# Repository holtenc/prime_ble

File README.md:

# Prime_EXL

An ergonomic bluetooth 45% keyboard with a macro/numpad added to the left side. 

Keyboard Maintainer: [Holtenc](https://github.com/holtenc/)  
Hardware Supported: Prime_ble PCB, ATMega32u4, NRF51822 
Hardware Availability: Prototype

Make example for this keyboard (after setting up your build environment):

    make handwired/prime_ble:default

See the [build environment setup](https://docs.qmk.fm/#/getting_started_build_tools) and the [make instructions](https://docs.qmk.fm/#/getting_started_make_guide) for more information. Brand new to QMK? Start with our [Complete Newbs Guide](https://docs.qmk.fm/#/newbs).

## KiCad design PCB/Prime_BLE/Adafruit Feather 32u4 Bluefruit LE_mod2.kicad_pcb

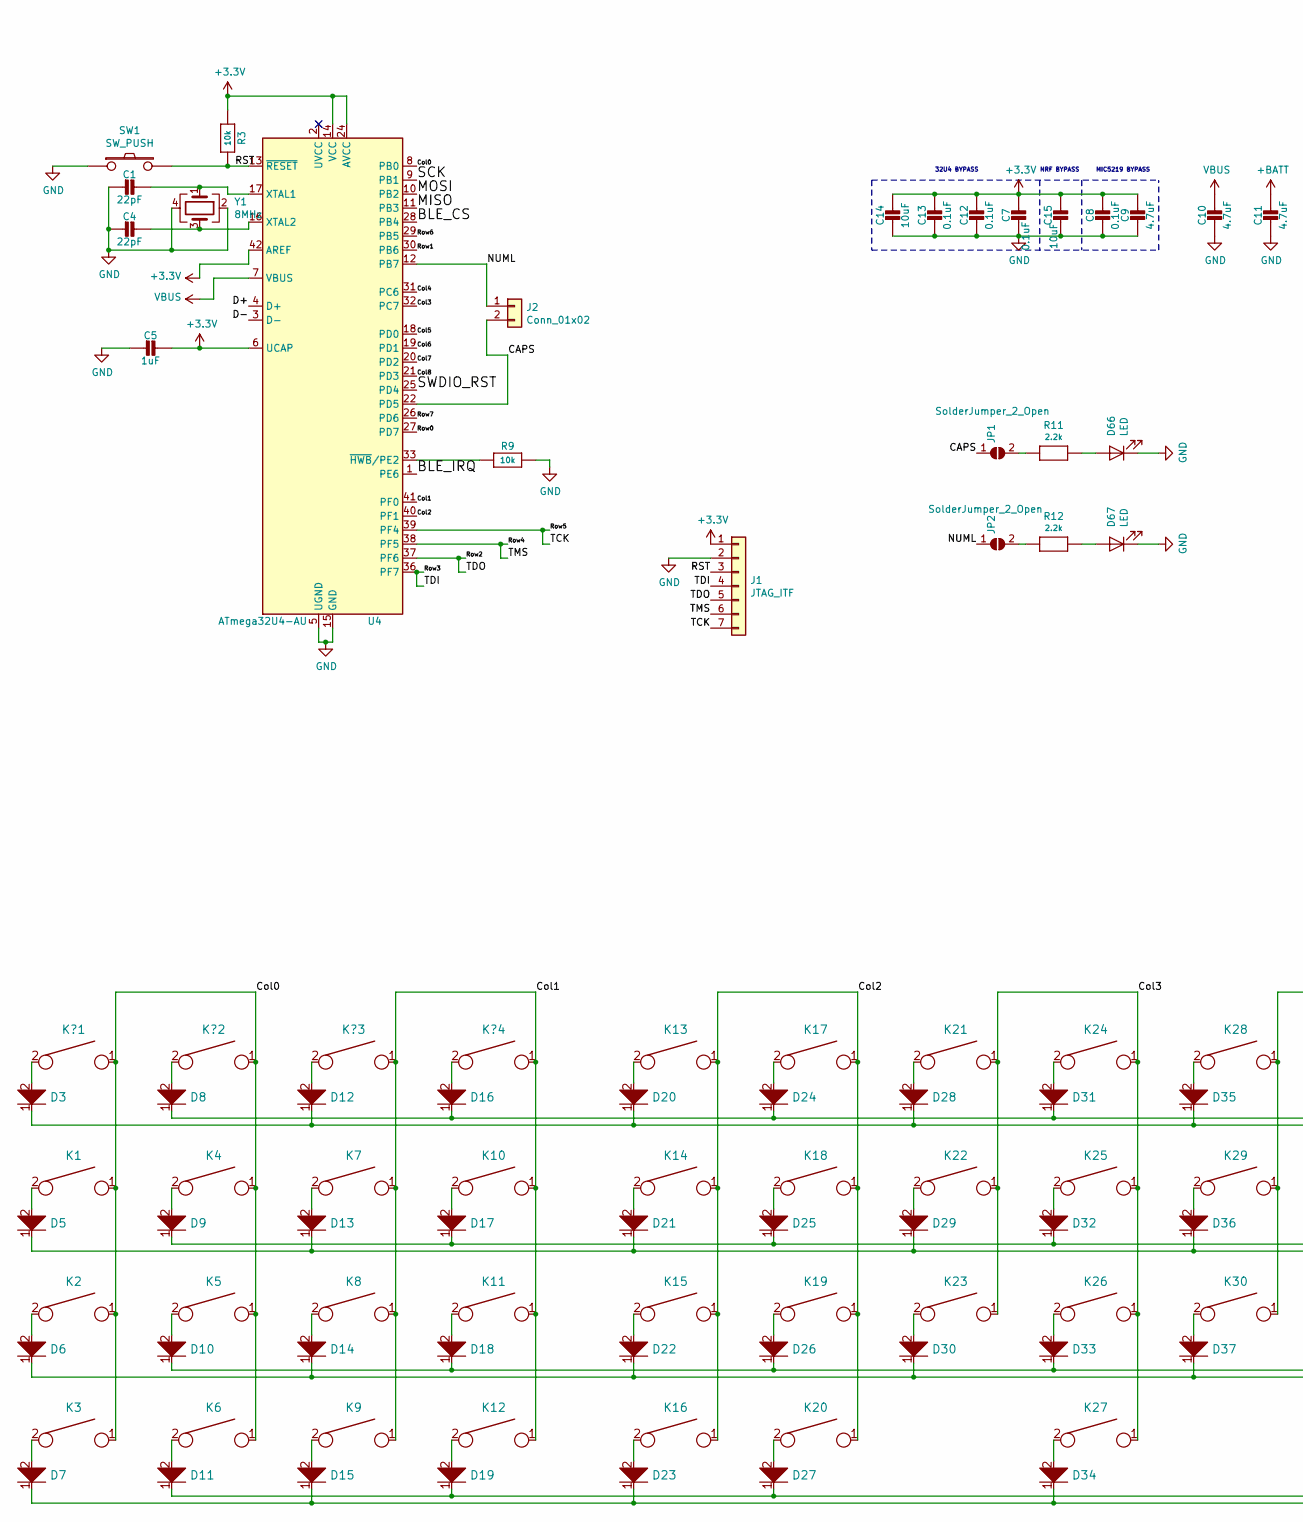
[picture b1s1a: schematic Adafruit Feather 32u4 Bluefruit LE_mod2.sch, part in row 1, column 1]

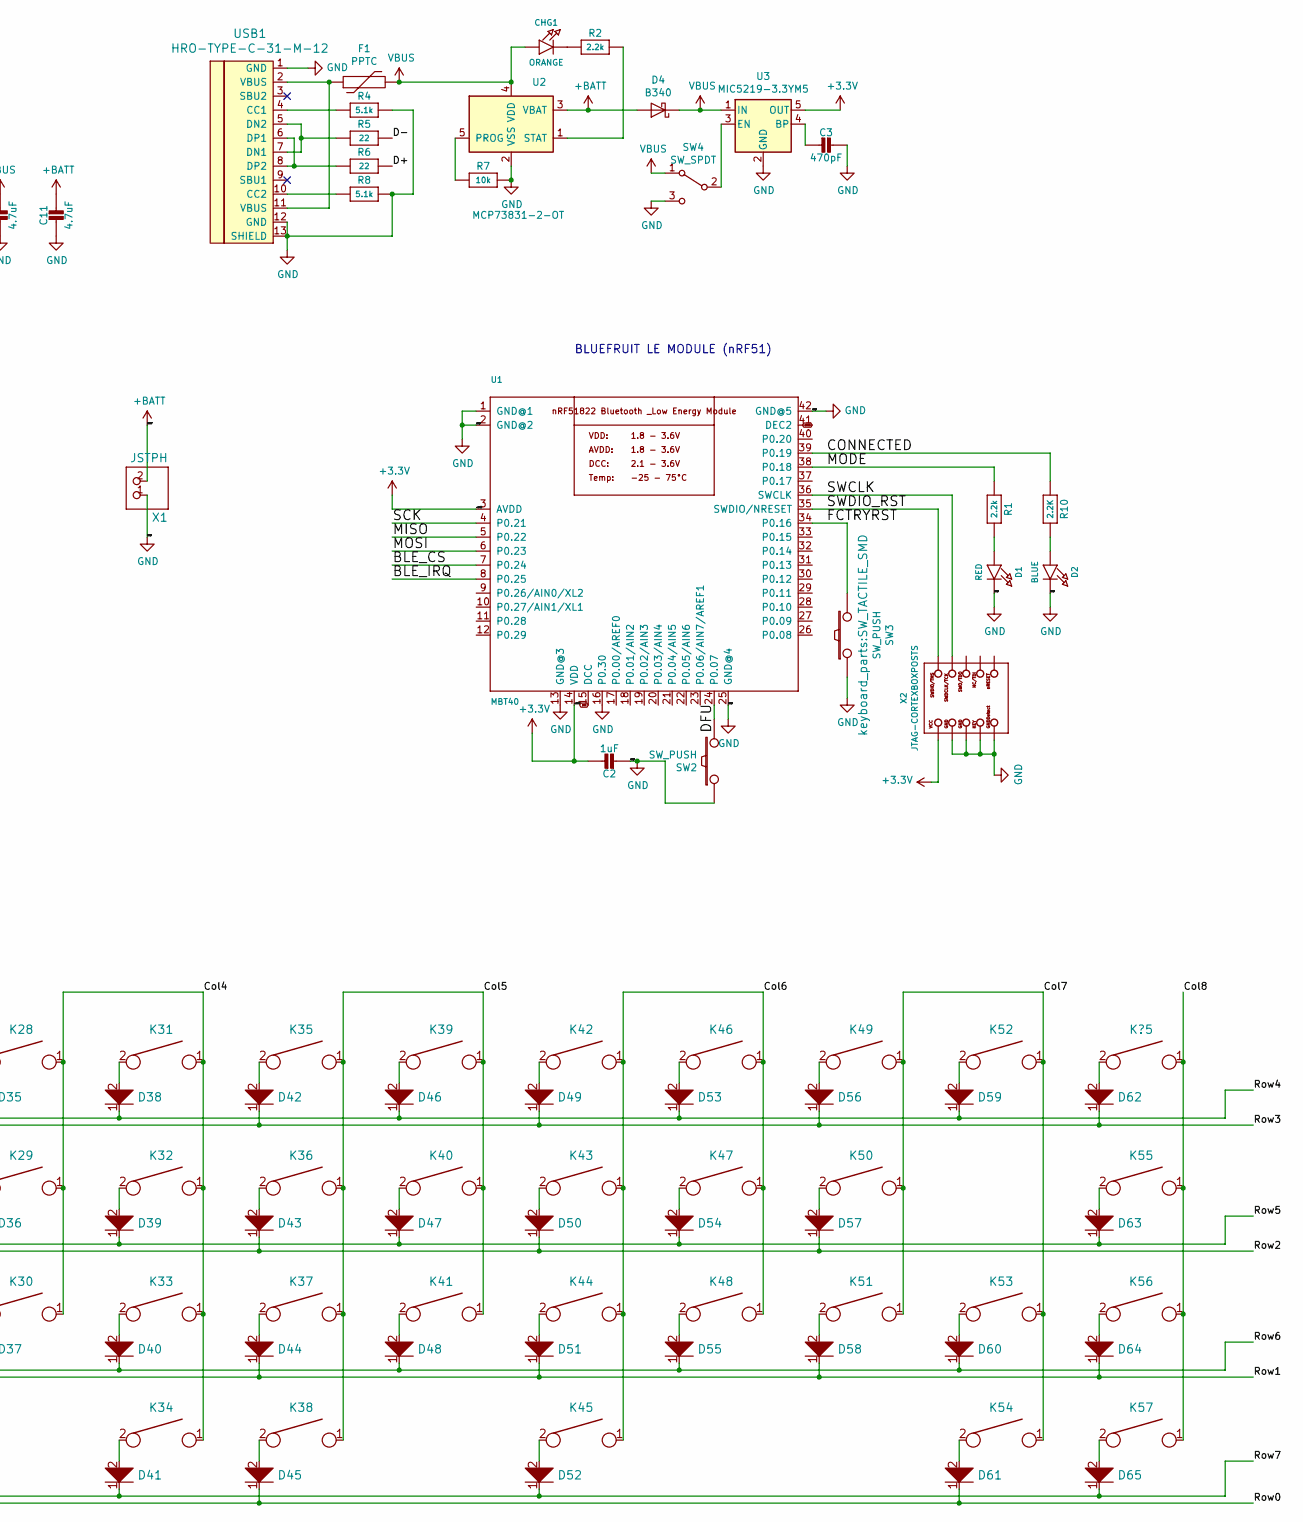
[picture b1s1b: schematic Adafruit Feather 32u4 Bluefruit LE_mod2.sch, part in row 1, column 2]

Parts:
C1, C4: 22pF; C_0603_1608Metric_Pad1.05x0.95mm_HandSolder
C2, C5: 1uF; C_0603_1608Metric_Pad1.05x0.95mm_HandSolder
C3: 470pF; C_0603_1608Metric_Pad1.05x0.95mm_HandSolder
C7, C8, C12, C13: 0.1uF; C_0603_1608Metric_Pad1.05x0.95mm_HandSolder
C9: 4.7uF; C_0603_1608Metric_Pad1.05x0.95mm_HandSolder
C10, C11: 4.7uF; C_1206_3216Metric_Pad1.42x1.75mm_HandSolder
C14, C15: 10uF; C_0603_1608Metric_Pad1.05x0.95mm_HandSolder
CHG1: ORANGE; IN-S124BR_LED
D1: RED; IN-S124BR_LED
D2: BLUE; IN-S124BR_LED
D3: D; D_SOD123
D4: B340; D_SMA_Handsoldering
D5, D6, D7, D8, D9, D10, D11, D12, D13, D14, D15, D16, D17, D18, D19, D20, D21, D22, D23, D24, D25, D26, D27, D28, D29, D30, D31, D32, D33, D34, D35, D36, D37, D38, D39, D40, D41, D42, D43, D44, D45, D46, D47, D48, D49, D50, D51, D52, D53, D54, D55, D56, D57, D58, D59, D60, D61, D62, D63, D64, D65: D; D_SOD-123
D66, D67: LED; IN-S124BR_LED
F1: PPTC; PPTC_nano
J1: JTAG_ITF; PinSocket_1x07_P2.54mm_Vertical
J2: Conn_01x02; PinSocket_1x02_P2.00mm_Vertical
JP1, JP2: SolderJumper_2_Open; SolderJumper-2_P1.3mm_Open_RoundedPad1.0x1.5mm
K1, K2, K3, K4, K5, K6, K7, K8, K9, K10, K11, K12, K13, K17, K18, K19, K21, K22, K23, K24, K25, K26, K28, K29, K30, K31, K32, K33, K35, K36, K37, K39, K40, K41, K42, K43, K44, K46, K47, K48, K49, K50, K51, K52, K53: KEYSW; CHERRY_PCB_100H
K14, K16, K20, K27, K45, K54, K56, K57: KEYSW; CHERRY_PCB_125H
K15, K55: KEYSW; CHERRY_PCB_175H
K34: KEYSW; CHERRY_PCB_200H
K38: KEYSW; CHERRY_PCB_225H
K?1, K?2, K?3, K?4, K?5: KEYSW; CHERRY_PCB_100H
R1, R2, R11, R12: 2.2k; R_0603_1608Metric
R3, R7, R9: 10k; R_0603_1608Metric
R4, R8: 5.1k; R_0603_1608Metric
R5, R6: 22; R_0603_1608Metric
R10: 2.2K; R_0603_1608Metric
SW1, SW2, SW3: SW_PUSH; SW_TACTILE_SMD
SW4: SW_SPDT; SW_EG1212
U1: MBT40; BLE_MODULE_RAYTAC_MDBT40
U2: MCP73831-2-OT; SOT-23-5
U3: MIC5219-3.3YM5; SOT-23-5
U4: ATmega32U4-AU; TQFP-44_10x10mm_P0.8mm
USB1: HRO-TYPE-C-31-M-12; HRO-TYPE-C-31-M-12-HandSoldering
X1: JSTPH; JSTPH2
X2: JTAG-CORTEXBOXPOSTS; 2X05_1.27MM_BOX_POSTS
Y1: 8MHz; Crystal_SMD_Abracon_ABM3B-4Pin_5.0x3.2mm

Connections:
+3V3: C2.1, C5.1, C7.1, C8.1, C9.1, C12.1, C13.1, C14.1, C15.1, J1.1, R3.1, U1.3 (AVDD), U1.14 (VDD), U3.5 (OUT), U4.6 (UCAP), U4.14 (VCC), U4.24 (AVCC), U4.34 (VCC), U4.42 (AREF), U4.44 (AVCC), X2.1 (VCC)
+BATT: C11.1, D4.2 (A), U2.3 (VBAT), X1.2
/BLE_CS: U1.7 (P0.24), U4.28 (PB4)
/BLE_IRQ: U1.8 (P0.25), U4.1 (PE6)
/CAPS: J2.2, JP1.1 (A), U4.22 (PD5)
/CONNECTED: R10.1, U1.39 (P0.19)
/Col1: K7.1, K8.1, K9.1, K10.1, K11.1, K12.1, K?3.1, K?4.1, U4.41 (PF0)
/Col2: K13.1, K14.1, K15.1, K16.1, K17.1, K18.1, K19.1, K20.1, U4.40 (PF1)
/Col3: K21.1, K22.1, K23.1, K24.1, K25.1, K26.1, K27.1, U4.32 (PC7)
/Col4: K28.1, K29.1, K30.1, K31.1, K32.1, K33.1, K34.1, U4.31 (PC6)
/Col5: K35.1, K36.1, K37.1, K38.1, K39.1, K40.1, K41.1, U4.18 (PD0)
/Col6: K42.1, K43.1, K44.1, K45.1, K46.1, K47.1, K48.1, U4.19 (PD1)
/Col7: K49.1, K50.1, K51.1, K52.1, K53.1, K54.1, U4.20 (PD2)
/Col8: K55.1, K56.1, K57.1, K?5.1, U4.21 (PD3)
/D+: R6.2, U4.4 (D+)
/D-: R5.2, U4.3 (D-)
/FCTRYRST: SW3.2, U1.34 (P0.16)
/MISO: U1.5 (P0.22), U4.11 (PB3)
/MODE: R1.1, U1.38 (P0.18)
/MOSI: U1.6 (P0.23), U4.10 (PB2)
/RST: J1.3, R3.2, SW1.2, U4.13 (~RESET)
/Row0: D7.1, D15.1, D23.1, D34.1, D45.1, D61.1, U4.27 (PD7)
/Row1: D6.1, D14.1, D22.1, D30.1, D37.1, D44.1, D51.1, D58.1, D64.1, U4.30 (PB6)
/Row2: D5.1, D13.1, D21.1, D29.1, D36.1, D43.1, D50.1, D57.1, J1.5, U4.37 (PF6)
/Row3: D3.1, D12.1, D20.1, D28.1, D35.1, D42.1, D49.1, D56.1, D62.1, J1.4, U4.36 (PF7)
/Row4: D8.1, D16.1, D24.1, D31.1, D38.1, D46.1, D53.1, D59.1, J1.6, U4.38 (PF5)
/Row5: D9.1, D17.1, D25.1, D32.1, D39.1, D47.1, D54.1, D63.1, J1.7, U4.39 (PF4)
/Row6: D10.1, D18.1, D26.1, D33.1, D40.1, D48.1, D55.1, D60.1, U4.29 (PB5)
/Row7: D11.1, D19.1, D27.1, D41.1, D52.1, D65.1, U4.26 (PD6)
/SCK: U1.4 (P0.21), U4.9 (PB1)
/SWCLK: U1.36 (SWCLK), X2.4 (SWDCLK)
/SWDIO_RST: U1.35 (SWDIO/NRESET), U4.25 (PD4), X2.2 (SWDIO)
DCC: U1.15 (DCC)
DEC2: U1.41 (DEC2)
unnamed: C1.1, U4.17 (XTAL1), Y1.1
unnamed: C3.2, U3.4 (BP)
unnamed: C4.1, U4.16 (XTAL2), Y1.3
unnamed: D1.2, D1.A, R1.2
unnamed: D2.2, D2.A, R10.2
unnamed: D3.2, K?1.2
unnamed: D5.2, K1.2
unnamed: D6.2, K2.2
unnamed: D7.2, K3.2
unnamed: D8.2, K?2.2
unnamed: D9.2, K4.2
unnamed: D10.2, K5.2
unnamed: D11.2, K6.2
unnamed: D12.2, K?3.2
unnamed: D13.2, K7.2
unnamed: D14.2, K8.2
unnamed: D15.2, K9.2
unnamed: D16.2, K?4.2
unnamed: D17.2, K10.2
unnamed: D18.2, K11.2
unnamed: D19.2, K12.2
unnamed: D20.2, K13.2
unnamed: D21.2, K14.2
unnamed: D22.2, K15.2
unnamed: D23.2, K16.2
unnamed: D24.2, K17.2
unnamed: D25.2, K18.2
unnamed: D26.2, K19.2
unnamed: D27.2, K20.2
unnamed: D28.2, K21.2
unnamed: D29.2, K22.2
unnamed: D30.2, K23.2
unnamed: D31.2, K24.2
unnamed: D32.2, K25.2
unnamed: D33.2, K26.2
unnamed: D34.2, K27.2
unnamed: D35.2, K28.2
unnamed: D36.2, K29.2
unnamed: D37.2, K30.2
unnamed: D38.2, K31.2
unnamed: D39.2, K32.2
unnamed: D40.2, K33.2
unnamed: D41.2, K34.2
unnamed: D42.2, K35.2
unnamed: D43.2, K36.2
unnamed: D44.2, K37.2
unnamed: D45.2, K38.2
unnamed: D46.2, K39.2
unnamed: D47.2, K40.2
unnamed: D48.2, K41.2
unnamed: D49.2, K42.2
unnamed: D50.2, K43.2
unnamed: D51.2, K44.2
unnamed: D52.2, K45.2
unnamed: D53.2, K46.2
unnamed: D54.2, K47.2
unnamed: D55.2, K48.2
unnamed: D56.2, K49.2
unnamed: D57.2, K50.2
unnamed: D58.2, K51.2
unnamed: D59.2, K52.2
unnamed: D60.2, K53.2
unnamed: D61.2, K54.2
unnamed: D62.2, K?5.2
unnamed: D63.2, K55.2
unnamed: D64.2, K56.2
unnamed: D65.2, K57.2
unnamed: D66.2 (A), R11.2
unnamed: F1.1, USB1.2 (VBUS), USB1.11 (VBUS)
unnamed: JP1.2 (B), R11.1
unnamed: JP2.2 (B), R12.1
unnamed: R2.2, U2.1 (STAT)
unnamed: R4.1, USB1.4 (CC1)
unnamed: R5.1, USB1.5 (DN2), USB1.7 (DN1)
unnamed: R6.1, USB1.6 (DP1), USB1.8 (DP2)
unnamed: R7.1, U2.5 (PROG)
unnamed: R8.1, USB1.10 (CC2)
unnamed: R9.1, U4.33 (~HWB~/PE2)
unnamed: SW2.2, U1.24 (P0.07)
unnamed: SW4.2 (B), U3.3 (EN)
VBUS: C10.1, CHG1.A, D4.1 (K), D67.2 (A), F1.2, R12.2, SW4.1 (A), U2.4 (VDD), U3.1 (IN), U4.7 (VBUS)

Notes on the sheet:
BLUEFRUIT LE MODULE (nRF51)
MIC5219 BYPASS
NRF BYPASS
32U4 BYPASS

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
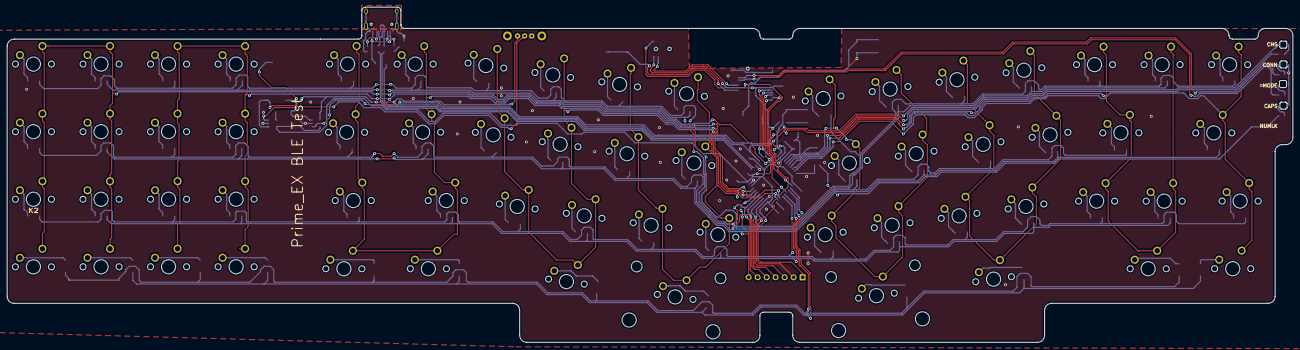
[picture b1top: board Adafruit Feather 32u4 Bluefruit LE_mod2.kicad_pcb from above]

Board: 2 copper layers, 362.4 x 94.4 mm, 169 parts (0 on the bottom side), 115 nets.

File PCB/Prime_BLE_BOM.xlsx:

Designator | Package | Quantity | Designation | Cost each | Total
D1 | IN-S124BR_LED | 1 |  | 0.3 | 0.3
D2 | IN-S124BR_LED | 1 |  | 0.3 | 0.3
CHG1 | IN-S124BR_LED | 1 |  | 0.3 | 0.3
D66,D67 | IN-S124BR_LED | 2 |  | 0.3 | 0.6
D3,D5,D6,D7,D8,D9,D10,D11,D12,D13,D14,D15,D16,D17,D18,D19,D20,D21,D22,D23,D24,D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 | D_SOD-123 | 62 |  | 0.1 | 6.2
SW4 | EG1213 | 1 | SW_SPDT | 0.65 | 0.65
C3 | 0603 | 1 | 470pF | 0.06 | 0.06
U4 | TQFP-44_10x10mm_P0.8mm | 1 | ATmega32U4-AU | 4.2 | 4.2
SW3,SW2,SW1 | TL3342F160 | 3 | SW_PUSH | 0.64 | 1.92
X2 | 2X05_1.27MM_BOX_POSTS | 1 | JTAG-CORTEXBOXPOSTS | 1.5 | 1.5
U1 | BLE_MODULE_RAYTAC_MDBT40 | 1 | MBT40 (adafruit 4076) | 7.5 | 7.5
X1 | JSTPH2 | 1 | S2B-PH-SM4-TB(LF)(SN) | 0.6 | 0.6
C1,C4 | 0603 | 2 | 22pF | 0.06 | 0.12
C5,C2 | 0603 | 2 | 1uF | 0.06 | 0.12
C7,C8,C12,C13 | 0603 | 4 | 0.1uF | 0.06 | 0.24
C9 | 0603 | 1 | 4.7uF | 0.06 | 0.06
C10,C11 | 1206 | 2 | 4.7uF | 0.2 | 0.4
F1 | PPTC_nano | 1 | 1206L050YR | 0.6 | 0.6
R3,R7,R9 | 0603 | 3 | 10k | 0.06 | 0.18
R4,R8 | 0603 | 2 | 5.1k | 0.06 | 0.12
R5,R6 | 0603 | 2 | 22 | 0.06 | 0.12
U2 | SOT-23-5 | 1 | MCP73831-2-OT | 0.6 | 0.6
U3 | SOT-23-5 | 1 | MIC5219-3.3YM5 | 1 | 1
USB1 | HRO-TYPE-C-31-M-12-HandSoldering | 1 | HRO-TYPE-C-31-M-12 | 0.5 | 0.5
Y1 | Crystal_SMD_Abracon_ABM3B-4Pin_5.0x3.2mm | 1 | 8MHz - 18pf | 1 | 1
R1,R10 | 0603 | 2 | 2.2K | 0.06 | 0.12
R2 | 0603 | 1 | 1K | 0.06 | 0.06
D4 | D_SMA_Handsoldering | 1 | B340AE-13 | 0.3 | 0.3
C14,C15 | 0603 | 2 | 10uF | 0.06 | 0.12
R11,R12 | 0603 | 2 | 1k | 0.06 | 0.12
 |  |  |  |  | 29.910000000000007

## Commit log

2019-06-25 re-arrange and update files
2019-06-25 add BOM
2019-06-26 update QMK firmware. add support for personal VIA build. organize folders
2020-09-30 fixed issues detailed in the master branch readme
2020-09-30 modify matrix pins
    modified matrix pins to match the issues corrected
2020-09-30 update keymap config
    update keymap config to reflect the changes made to the matrix
2020-09-30 update keymap config
    update keymap config to reflect changes in the matrix
